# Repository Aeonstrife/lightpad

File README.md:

# lightpad
 drop-in replacement pcb for Duck Lightpad

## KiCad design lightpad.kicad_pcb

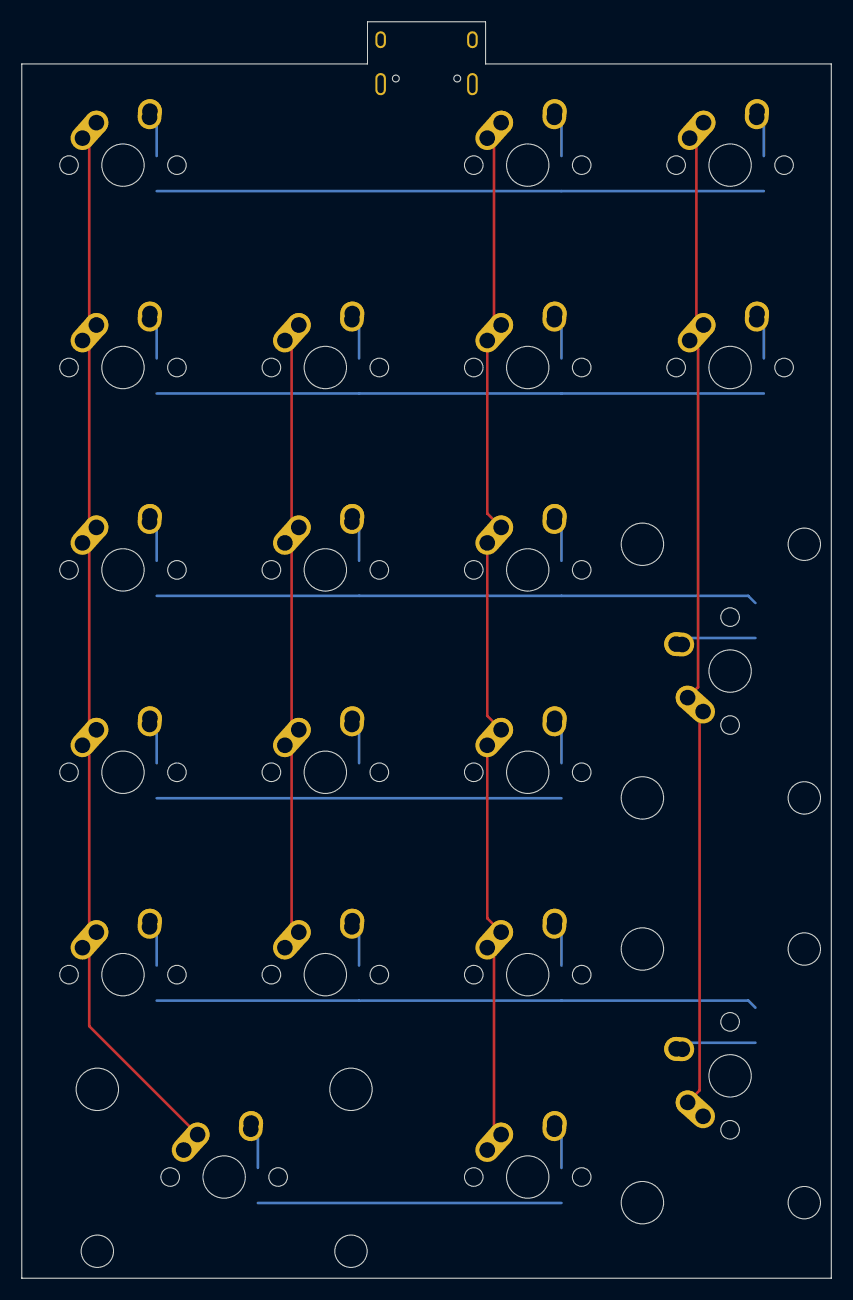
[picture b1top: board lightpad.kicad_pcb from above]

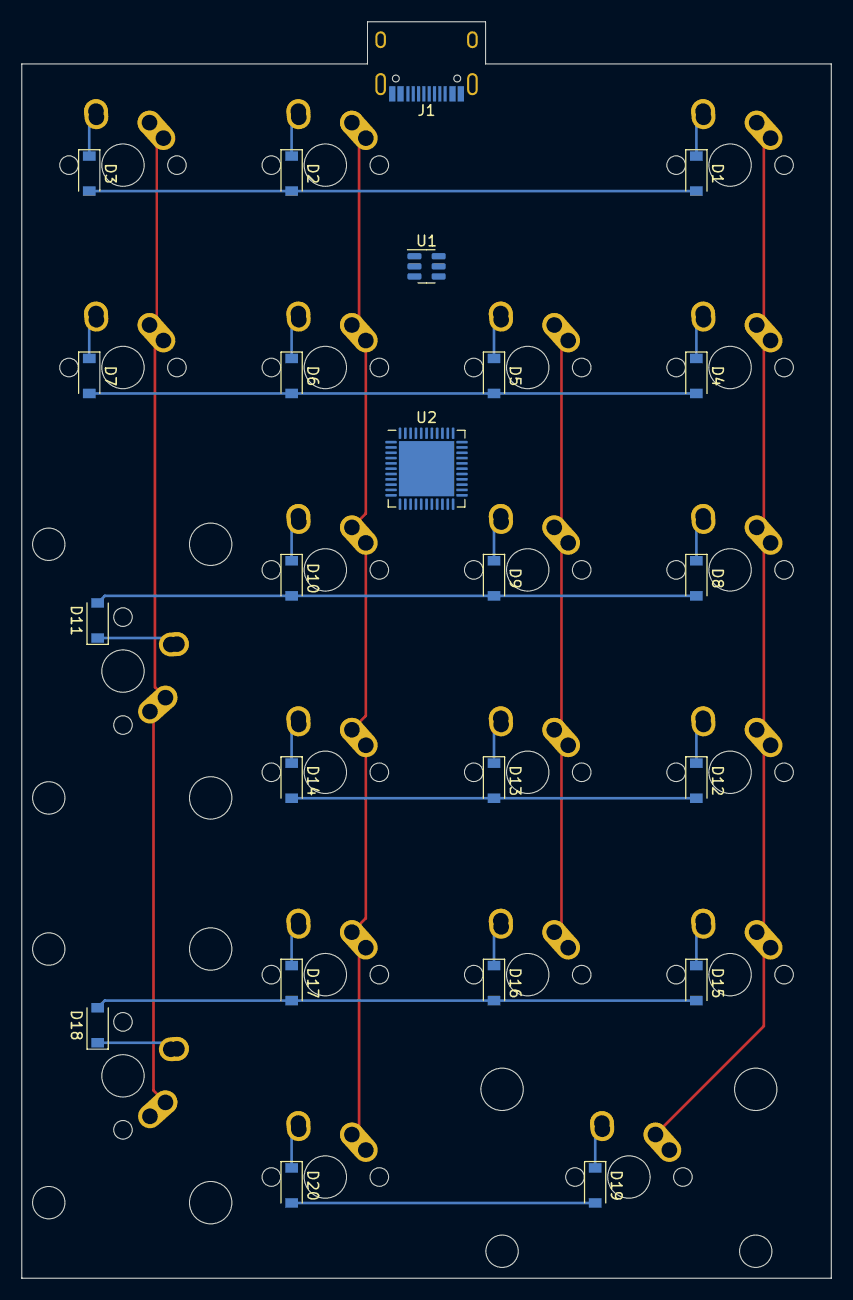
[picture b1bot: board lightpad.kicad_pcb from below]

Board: 2 copper layers, 76.2 x 118.3 mm, 43 parts (23 on the bottom side), 33 nets.

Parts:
D1, D2, D3, D4, D5, D6, D7, D8, D9, D10, D11, D12, D13, D14, D15, D16, D17, D18, D19, D20: 1N4148W; D_SOD-123
J1: USB_C_Receptacle_USB2.0; HRO-TYPE-C-31-M-12
MX1, MX2, MX3, MX4, MX5, MX6, MX7, MX8, MX9, MX10, MX12, MX13, MX14, MX15, MX16, MX17, MX20: MX-NoLED; MX-1U-NoLED
MX11, MX18, MX19: MX-NoLED; MX-2U-ReversedStabilizers-NoLED
U1: SRV05-4; SOT-23-6
U2: ATmega32U4-M; QFN-44-1EP_7x7mm_P0.5mm_EP5.2x5.2mm

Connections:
COL0: MX1.1 (COL), MX4.1 (COL), MX8.1 (COL), MX12.1 (COL), MX15.1 (COL), MX19.1 (COL)
COL1: MX5.1 (COL), MX9.1 (COL), MX13.1 (COL), MX16.1 (COL)
COL2: MX2.1 (COL), MX6.1 (COL), MX10.1 (COL), MX14.1 (COL), MX17.1 (COL), MX20.1 (COL)
COL3: MX3.1 (COL), MX7.1 (COL), MX11.1 (COL), MX18.1 (COL)
unnamed: D1.1 (K), MX1.2 (ROW)
unnamed: D2.1 (K), MX2.2 (ROW)
unnamed: D3.1 (K), MX3.2 (ROW)
unnamed: D4.1 (K), MX4.2 (ROW)
unnamed: D5.1 (K), MX5.2 (ROW)
unnamed: D6.1 (K), MX6.2 (ROW)
unnamed: D7.1 (K), MX7.2 (ROW)
unnamed: D8.1 (K), MX8.2 (ROW)
unnamed: D9.1 (K), MX9.2 (ROW)
unnamed: D10.1 (K), MX10.2 (ROW)
unnamed: D11.1 (K), MX11.2 (ROW)
unnamed: D12.1 (K), MX12.2 (ROW)
unnamed: D13.1 (K), MX13.2 (ROW)
unnamed: D14.1 (K), MX14.2 (ROW)
unnamed: D15.1 (K), MX15.2 (ROW)
unnamed: D16.1 (K), MX16.2 (ROW)
unnamed: D17.1 (K), MX17.2 (ROW)
unnamed: D18.1 (K), MX18.2 (ROW)
unnamed: D19.1 (K), MX19.2 (ROW)
unnamed: D20.1 (K), MX20.2 (ROW)
unnamed: U2.14 (VCC), U2.34 (VCC)
unnamed: U2.15 (GND), U2.23 (GND), U2.35 (GND), U2.43 (GND), U2.45 (GND)
unnamed: U2.24 (AVCC), U2.44 (AVCC)
ROW0: D1.2 (A), D2.2 (A), D3.2 (A)
ROW1: D4.2 (A), D5.2 (A), D6.2 (A), D7.2 (A)
ROW2: D8.2 (A), D9.2 (A), D10.2 (A), D11.2 (A)
ROW3: D12.2 (A), D13.2 (A), D14.2 (A)
ROW4: D15.2 (A), D16.2 (A), D17.2 (A), D18.2 (A)
ROW5: D19.2 (A), D20.2 (A)

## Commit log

2022-11-12 Add submodules
2022-11-12 Init files
